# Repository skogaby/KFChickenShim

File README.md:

# KFChickenShim - Make your Sound Voltex 4 cabinet feel new again

So, you bought a Sound Voltex 4 cabinet, but weren't able to secure an official or clone upgrade kit for Sound Voltex V?

This is **KFChickenShim**, a simple PCB that adapts the various JST connectors found on a Sound Voltex IV IO board (known as **KFCA**) to standard connectors that allow you to easily connect the board to an off-the-shelf PC. Doing this, you can utilize a solution known as **KFChicken**, combined with **SpiceTools**, to run SDVX 5 or newer inside an older cabinet, complete with full IO, card reader, working lights, headphone support, etc. In addition, there is no perceivable latency or negative affect on gameplay, though your in-game offsets may not be what you're typically used to and might need adjustment for the new setup.

## Requirements

If you buy a pre-made PCB from me, you'll need the following:

* A KFChickenShim PCB (plus the components below)
  * DB9 serial cable. (**NOTE:** I've had better luck using DB9 serial -> USB cables, instead of using my motherboard's onboard serial port)
  * 3.5mm audio cable
  * 12v DC power adapter (5.5mm barrel jack connector)
* A newer PC that's powerful enough to run SDVX 5
* SpiceTools + KFChicken

Additionally, if you're ordering and assembling your own PCB, you'll need the following connectors:
* JST VH (6-pin and 7-pin)
* JST XAD (2x5-pin)
* 3x 2.5mm or 2.54mm pins (for the audio, I couldn't identify the exact JST connector Konami used for this but bare pins work fine)
* 5.5mm DC power barrel jack
* Sparkfun DB9 serial port (others might fit but the footprint was for this one, specifically)
  * https://www.sparkfun.com/products/429
* Sparkfun 3.5mm audio port (others might fit but the footprint was for this one, specifically)
  * https://www.sparkfun.com/products/8032

## Setup

Here are the instructions for setting up the board for use. I will not cover PCB assembly, all of the components are pretty self-explanatory in terms of placement on the board (they all have exactly one spot).

### Hardware Setup

#### Step 1: PC Removal

The first thing you'll want to do is remove the original BemaniPC from the cabinet. You'll need to disconnect every cable and remove the PC **entirely**, as the KFCA board is inside the PC case. In the below image, the board in the red rectangle is the one we're after.

#### Step 2: Removing the KFCA board

Once the PC is removed from the cabinet, you'll need to remove the KFCA board from inside the PC case, which means you'll need to unscrew the case of the BemaniPC so you can get inside it. **NOTE**: If your cab is a gen 1 cabinet, your PC may look different from mine, but the process should be similar in terms of removing the IO.

Once the top is removed, you should see the exposed motherboard of the original PC. You'll more or less want to unplug all cables from the motherboard, to make it easy to remove since the KFCA sits underneath the motherboard. In the picture below, the connector in the red rectangle is the serial coming from the KFCA, and will be plugged into the KFChickenShim board.

Once the motherboard is removed entirely, you'll be greeted with a view similar to below.

Go ahead and remove the metal plate that the motherboard was mounted to. Below it, you should see the KFCA board itself, as well as the power supply unit for the PC and the KFCA board.

***KFCA Board***

***Power supply, with power connectors for the KFCA board***

Once you unscrew the KFCA board, it should be free and ready for use.

Below is the wiring harness that you should now have onhand for the KFCA board. Yours probably also has a plug that previously powered the PC, I just cut that off of mine since it's no longer being used. The wiring harness in the image is labeled appropriately, as we'll be referring to these later during assembly.

#### Step 3: Installing the KFCA to the new PC

**NOTE:** I am *NOT* going to cover how to install the PC itself into your cabinet. This step can vary wildly depending on your setup. However, here is a picture of my personal cabinet, with a new PC installed and the IO removed. Please note that most cabinets have a 120v passthrough outlet sort of dangling at the end of a cord inside the cabinet. I highly recommend using this to power everything, but I had to pull that cable out of my cab for a different machine that needed one, so I spliced a regular wall outlet into the cab's power supply's 120v out. If you go this route, install an outlet cover box over the outlet (not pictured here).

I'd also recommend making some sort of board like below with actual PCB/motherboard standoffs screwed into the wood. This will let you mount the PCBs inside the cab cleanly.

Go ahead and hook up the cables to the KFCA that are dangling inside the cabinet that previously connected to the front of the BemaniPC.

Next, connect the power connections from the KFChickenShim board to the KFCA via the wiring harness pulled from the original cabinet. Yellow is 12v, black is ground.

Now connect the power cable to the KFCA board itself from the wiring harness.

Next, connect the wiring harness power for the cabinet fan that sits next to the PC.

Connect the audio connector that's inside the cabinet (should be connected to 3 sets of red/white RCA cables on the other end) to the KFChickenShim board. Note the orientation of the plug, if it's plugged in backwards your left and right audio will be swapped.

Connect the card reader to the wiring harness from the KFCA.

Connect the serial from the wiring harness to the KFChickenShim board.

Connect this plug from the wiring harness to the KFCA board.

Connect the power input, serial cable, and audio cables to the KFChickenShim board and connect it to the new PC.

Almost there! I'd recommend mounting the board like this to the inside of the cabinet rear panel. I used velcro strip to attach the board to the rear door, in case I need to remove the rear door entirely.

If you power the cabinet on, you should see one red light on the KFCA, as well as one flashing light. 

Hopefully this is the end of your hardware journey. Read the notes below for important tips when installing the software side of things.

#### Step 4: Setting up the software

Generally, just follow the KFChicken release thread's instructions for setting everything up, but here's a quick rundown and ***note the bolded item in particular:***
* Copy the `libacio.dll` file from your SDVX 4 installation and paste it into your SDVX 5 installation, renaming it to `libacio32.dll`.
* Copy `kfchicken32.dll` and `kfchicken32.exe` into your SDVX 5 installation. The KFChicken release thread says you can use the 64-bit version and the SDVX 5 DLLs but this doesn't work correctly as of this writing, so use the SDVX 4 modules and 32-bit KFChicken.
* Setup your `kfchicken.json` file as below, making sure to change the `com` field to the appropriate COM port to match whatever serial port the KFCA is hooked up to (can be found using Windows Device Manager, under `Ports (COM and LPT)`), and also the right settings to match your SpiceAPI port and password in `gamestart.bat` (covered next). **NOTE: The default `kfchicken.json` file has the `baudrate` field set to `57600`. I personally experienced unplayable knobs/analog inputs until I changed this value to `115200` instead.**
```json
{
  "acio_dll": "libacio32.dll",
  "com": 2,
  "baudrate": 115200,
  "host": "localhost",
  "port": 1337,
  "pass": "changeme",
  "boot_delay": 500,
  "poll_delay": 0,
  "soft_fail": false,
  "parse_cmd_line_args": true,
  "debug_hook": false,
  "watchdog_enable": false,
  "watchdog_time": 120000,
  "icca_enable": true,
  "icca_limit": 1500,
  "kfca_enable": true,
  "coin_enable": true,
  "coin_blocker_delay": 500,
  "volume_enable": true,
  "volume_sync": true,
  "volume_sound_default": 20,
  "volume_sound_limit": 0,
  "volume_woofer_default": 20,
  "volume_external_default": 100,
  "volume_headphone_default": 20,
  "lcdhandle_enable": true,
  "lcdhandle_port": "COM2",
  "lcdhandle_delay": 200
}
```
* Modify your `gamestart.bat` file to start KFChicken before starting Spice, and also to make Spice expose its API. Change the port and password to whatever you'd like, but make sure the `kfchicken.json` file has the same settings.
```bat
start ./kfchicken32.exe
start ./spice64.exe -api 1337 -apipass changeme -sdvx
```
* If all went well, you should finally be good to go, and SDVX 5 will be running using the old IO board!

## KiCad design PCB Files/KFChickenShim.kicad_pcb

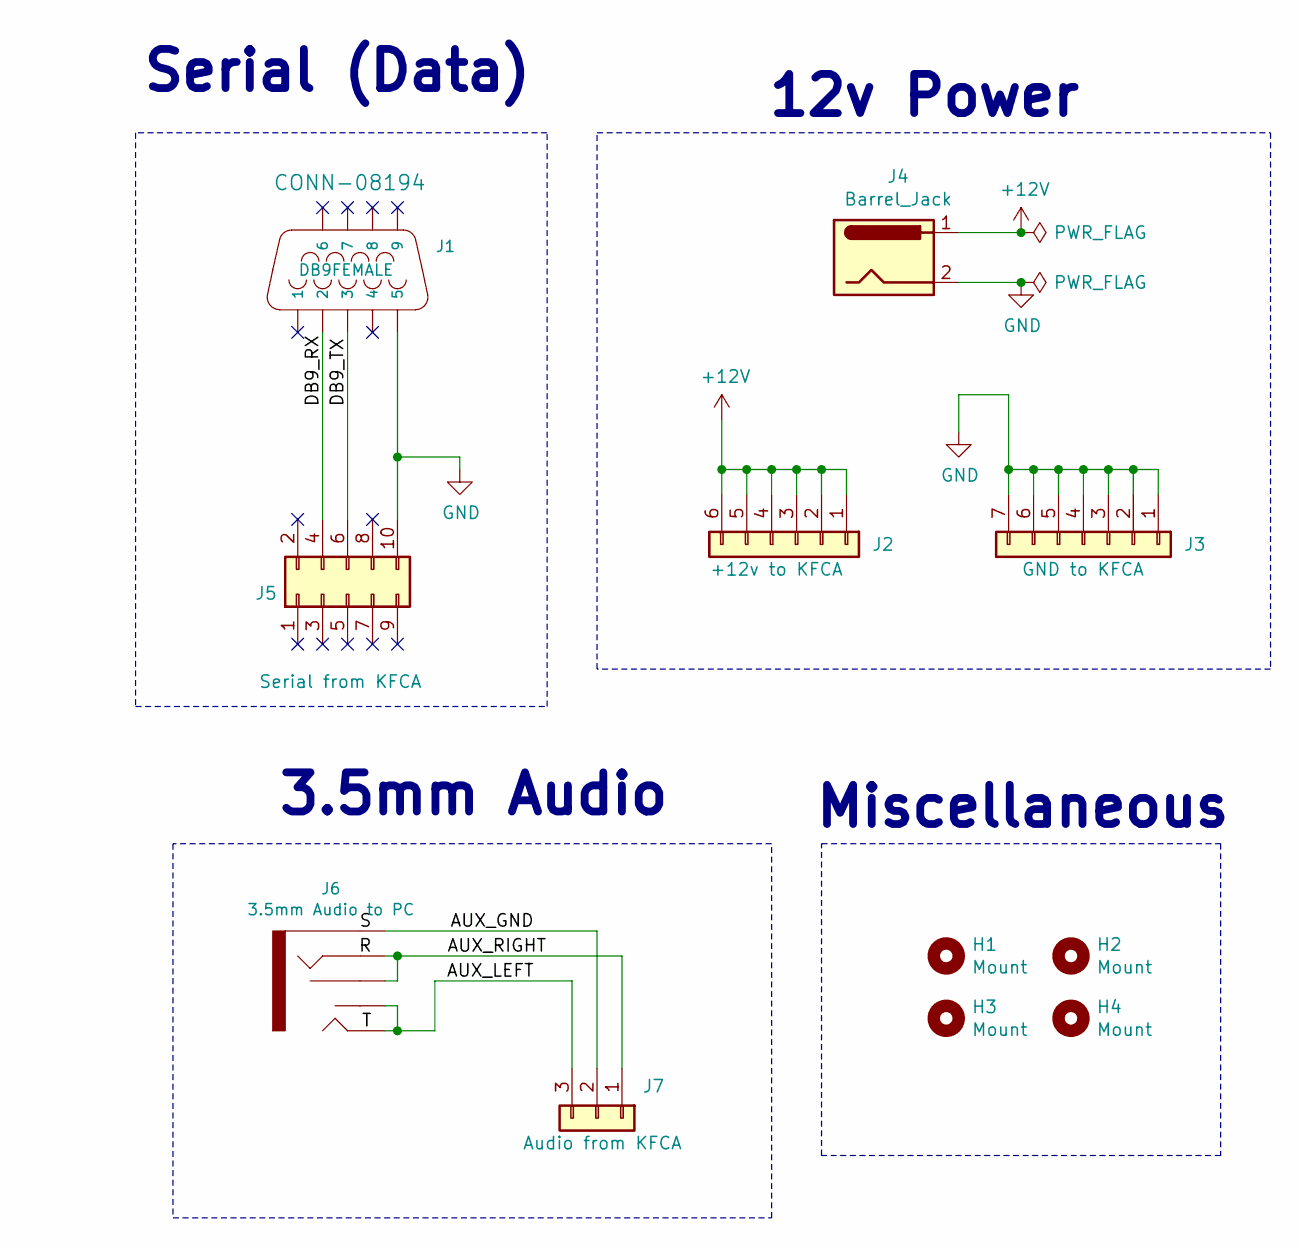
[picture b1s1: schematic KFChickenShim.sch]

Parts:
H1, H2, H3, H4: Mount; MountingHole_3.2mm_M3_Pad
J1: DB9FEMALE; DB9
J2: +12v to KFCA; JST_VH_B6P-VH_1x06_P3.96mm_Vertical
J3: GND to KFCA; JST_VH_B7P-VH_1x07_P3.96mm_Vertical
J4: Barrel_Jack; BarrelJack_Horizontal
J5: Serial from KFCA; JST_XAD_B10B-XADSS-N_2x05_P2.50mm_Vertical
J6: 3.5mm Audio to PC; AUDIO-JACK
J7: Audio from KFCA; JST_XH_B3B-XH-A_1x03_P2.50mm_Vertical

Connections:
+12V: J2.1, J2.2, J2.3, J2.4, J2.5, J2.6, J4.1
/AUX_GND: J6.SLEE (SLEEVE), J7.2
/AUX_LEFT: J6.TIP, J6.TSH, J7.3
/AUX_RIGHT: J6.RING, J6.RSH, J7.1
/DB9_RX: J1.2, J5.4
/DB9_TX: J1.3, J5.6
GND: J1.5, J3.1, J3.2, J3.3, J3.4, J3.5, J3.6, J3.7, J4.2, J5.10

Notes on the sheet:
Serial (Data)
12v Power
3.5mm Audio
Miscellaneous

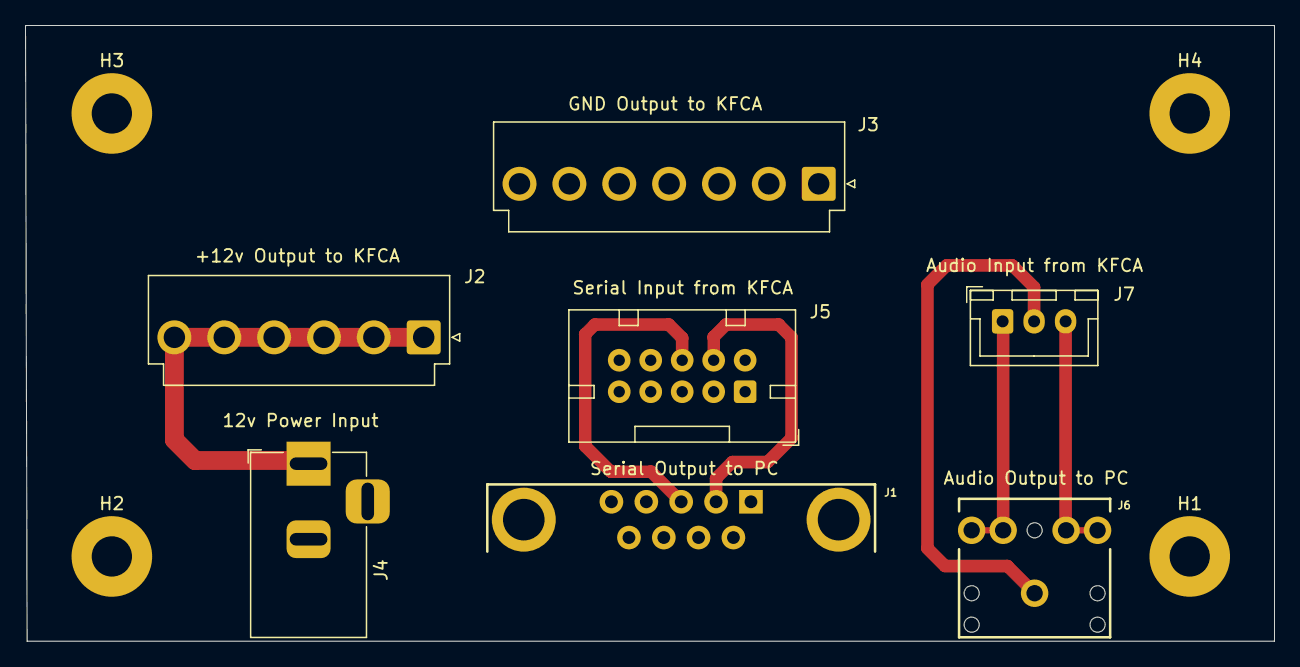
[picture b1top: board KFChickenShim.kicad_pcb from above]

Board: 2 copper layers, 99.2 x 48.9 mm, 11 parts (0 on the bottom side), 7 nets.

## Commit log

2021-04-12 Real initial commit. PCB files + first pass guide
2021-04-12 Fix README image links
2021-04-12 Readme fixes
